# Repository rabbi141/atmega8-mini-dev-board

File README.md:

# AVR ATmega8 Mini Devlopment Board

The PCB of this board is designed with KiCad V5

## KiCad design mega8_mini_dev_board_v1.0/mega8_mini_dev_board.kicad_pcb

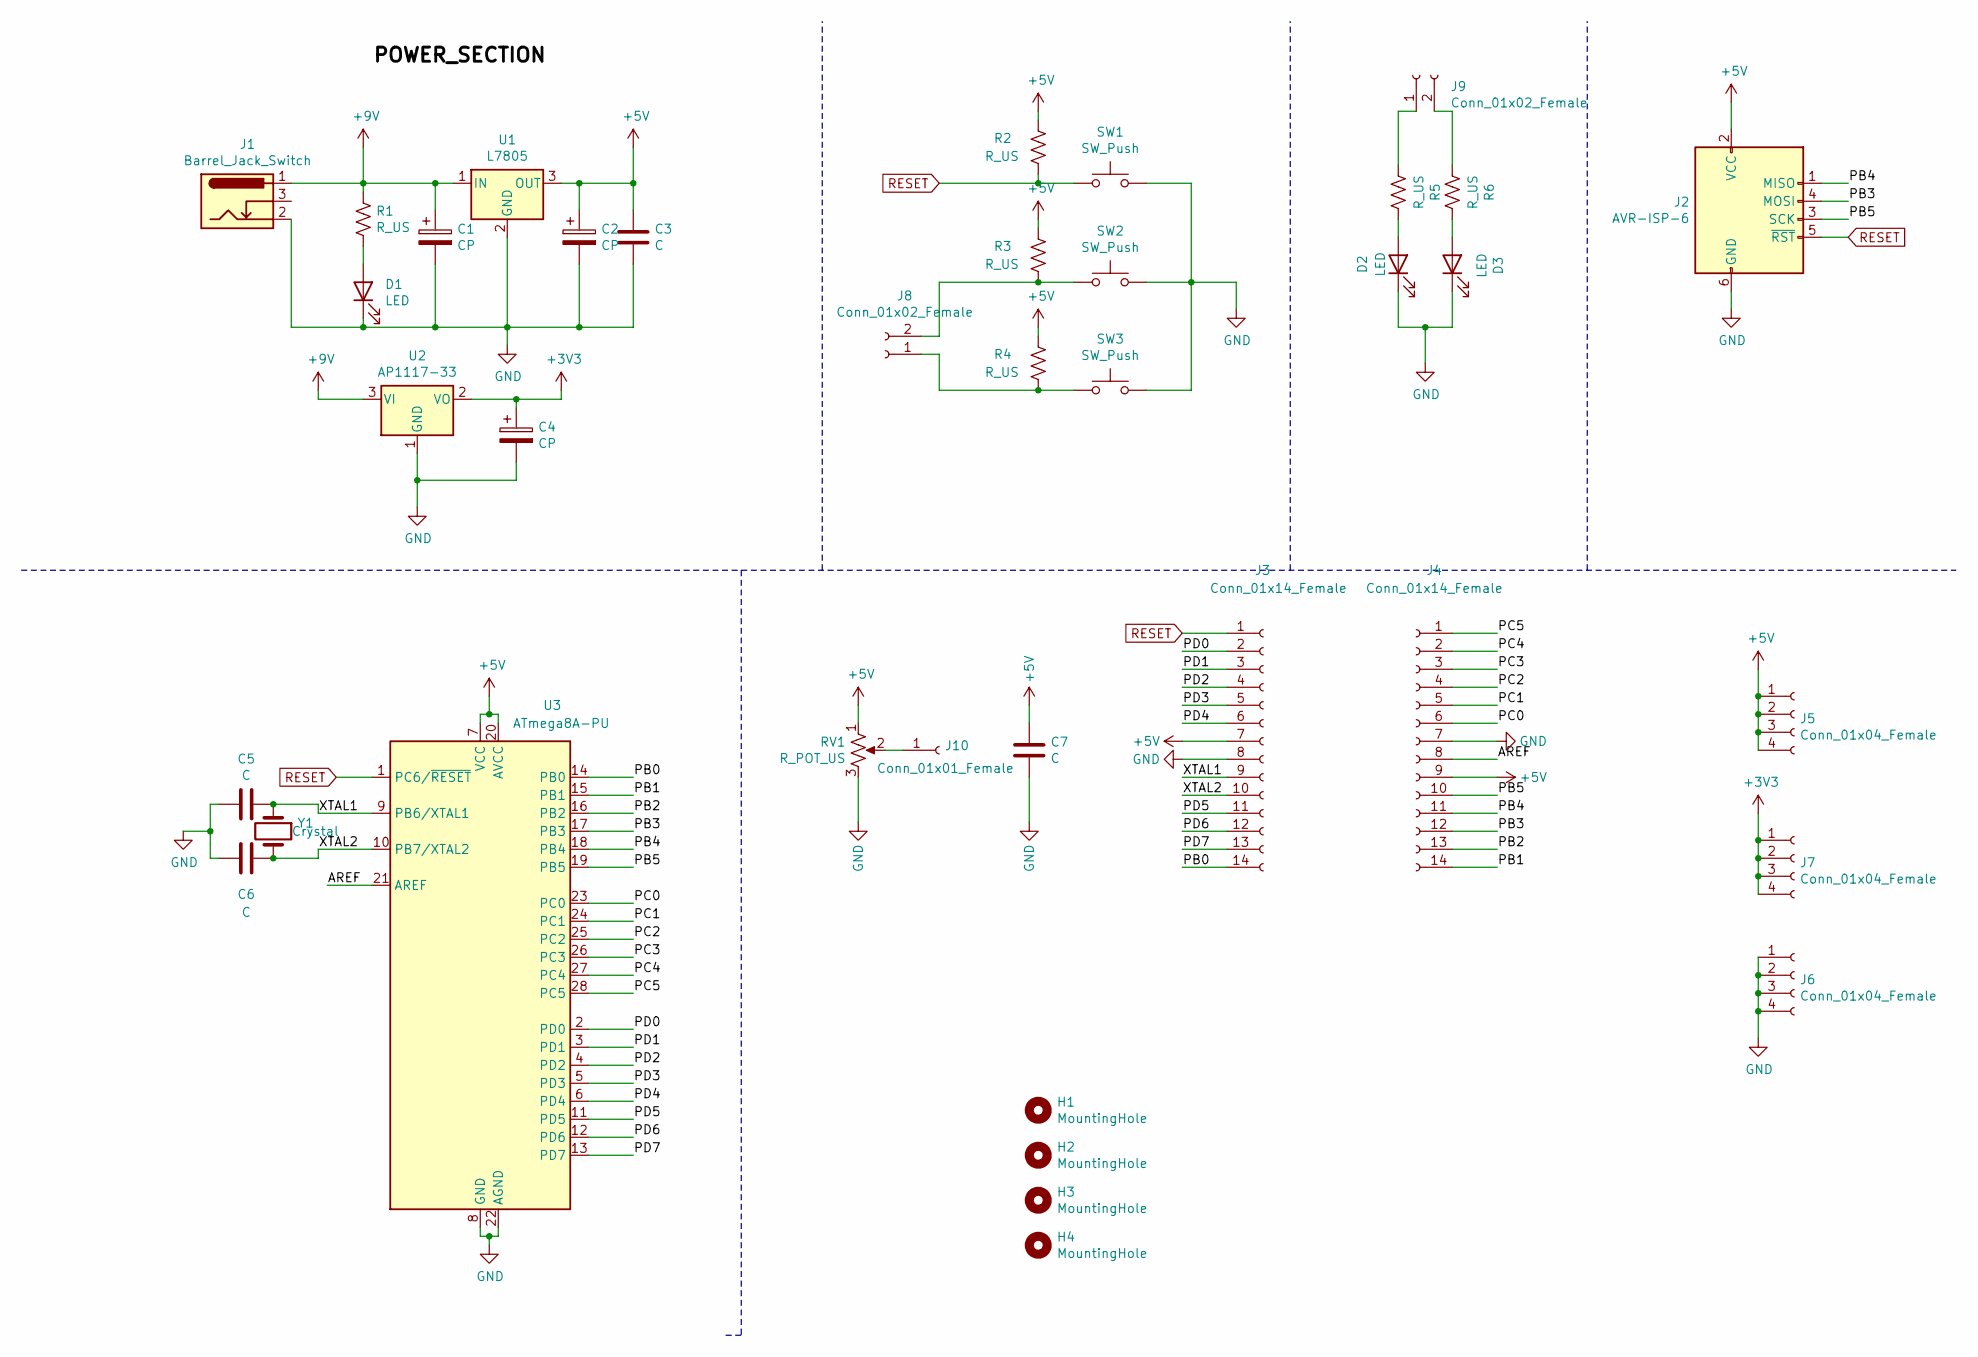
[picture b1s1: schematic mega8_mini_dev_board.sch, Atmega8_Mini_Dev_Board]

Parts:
C1, C2, C4: CP; CP_Radial_D6.3mm_P2.50mm
C3, C5, C6, C7: C; C_Disc_D5.0mm_W2.5mm_P2.50mm
D1, D2, D3: LED; LED_D3.0mm
H1, H2, H3, H4: MountingHole; MountingHole_3mm_Pad
J1: Barrel_Jack_Switch; BarrelJack_Horizontal
J2: AVR-ISP-6; IDC-Header_2x03_P2.54mm_Vertical
J3, J4: Conn_01x14_Female; PinSocket_1x14_P2.54mm_Vertical
J5, J6, J7: Conn_01x04_Female; PinSocket_1x04_P2.54mm_Vertical
J8, J9: Conn_01x02_Female; PinSocket_1x02_P2.54mm_Vertical
J10: Conn_01x01_Female; PinSocket_1x01_P2.54mm_Vertical
R1, R2, R3, R4, R5, R6: R_US; R_Axial_DIN0207_L6.3mm_D2.5mm_P10.16mm_Horizontal
RV1: R_POT_US; Potentiometer_ACP_CA9-V10_Vertical
SW1, SW2, SW3: SW_Push; SW_PUSH_6mm
U1: L7805; TO-220-3_Vertical
U2: AP1117-33; SOT-223-3_TabPin2
U3: ATmega8A-PU; DIP-28_W7.62mm
Y1: Crystal; Crystal_HC52-8mm_Vertical

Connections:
+3V3: C4.1, J7.1, J7.2, J7.3, J7.4, U2.2 (VO)
+5V: C2.1, C3.1, C7.1, J2.2 (VCC), J3.7, J4.9, J5.1, J5.2, J5.3, J5.4, R2.2, R3.2, R4.2, RV1.1, U1.3 (OUT), U3.7 (VCC), U3.20 (AVCC)
+9V: C1.1, J1.1, R1.2, U1.1 (IN), U2.3 (VI)
/AREF: J4.8, U3.21 (AREF)
/PB0: J3.14, U3.14 (PB0)
/PB1: J4.14, U3.15 (PB1)
/PB2: J4.13, U3.16 (PB2)
/PB3: J2.4 (MOSI), J4.12, U3.17 (PB3)
/PB4: J2.1 (MISO), J4.11, U3.18 (PB4)
/PB5: J2.3 (SCK), J4.10, U3.19 (PB5)
/PC0: J4.6, U3.23 (PC0)
/PC1: J4.5, U3.24 (PC1)
/PC2: J4.4, U3.25 (PC2)
/PC3: J4.3, U3.26 (PC3)
/PC4: J4.2, U3.27 (PC4)
/PC5: J4.1, U3.28 (PC5)
/PD0: J3.2, U3.2 (PD0)
/PD1: J3.3, U3.3 (PD1)
/PD2: J3.4, U3.4 (PD2)
/PD3: J3.5, U3.5 (PD3)
/PD4: J3.6, U3.6 (PD4)
/PD5: J3.11, U3.11 (PD5)
/PD6: J3.12, U3.12 (PD6)
/PD7: J3.13, U3.13 (PD7)
/XTAL1: C5.1, J3.9, U3.9 (PB6/XTAL1), Y1.1
/XTAL2: C6.1, J3.10, U3.10 (PB7/XTAL2), Y1.2
GND: C1.2, C2.2, C3.2, C4.2, C5.2, C6.2, C7.2, D1.1 (K), D2.1 (K), D3.1 (K), J1.2, J2.6 (GND), J3.8, J4.7, J6.1, J6.2, J6.3, J6.4, RV1.3, SW1.2, SW2.2, SW3.2, U1.2 (GND), U2.1 (GND), U3.8 (GND), U3.22 (AGND)
unnamed: D1.2 (A), R1.1
unnamed: D2.2 (A), R5.2
unnamed: D3.2 (A), R6.2
unnamed: J8.1, R4.1, SW3.1
unnamed: J8.2, R3.1, SW2.1
unnamed: J9.1, R5.1
unnamed: J9.2, R6.1
unnamed: J10.1, RV1.2
RESET: J2.5 (~RST), J3.1, R2.1, SW1.1, U3.1 (PC6/~RESET)

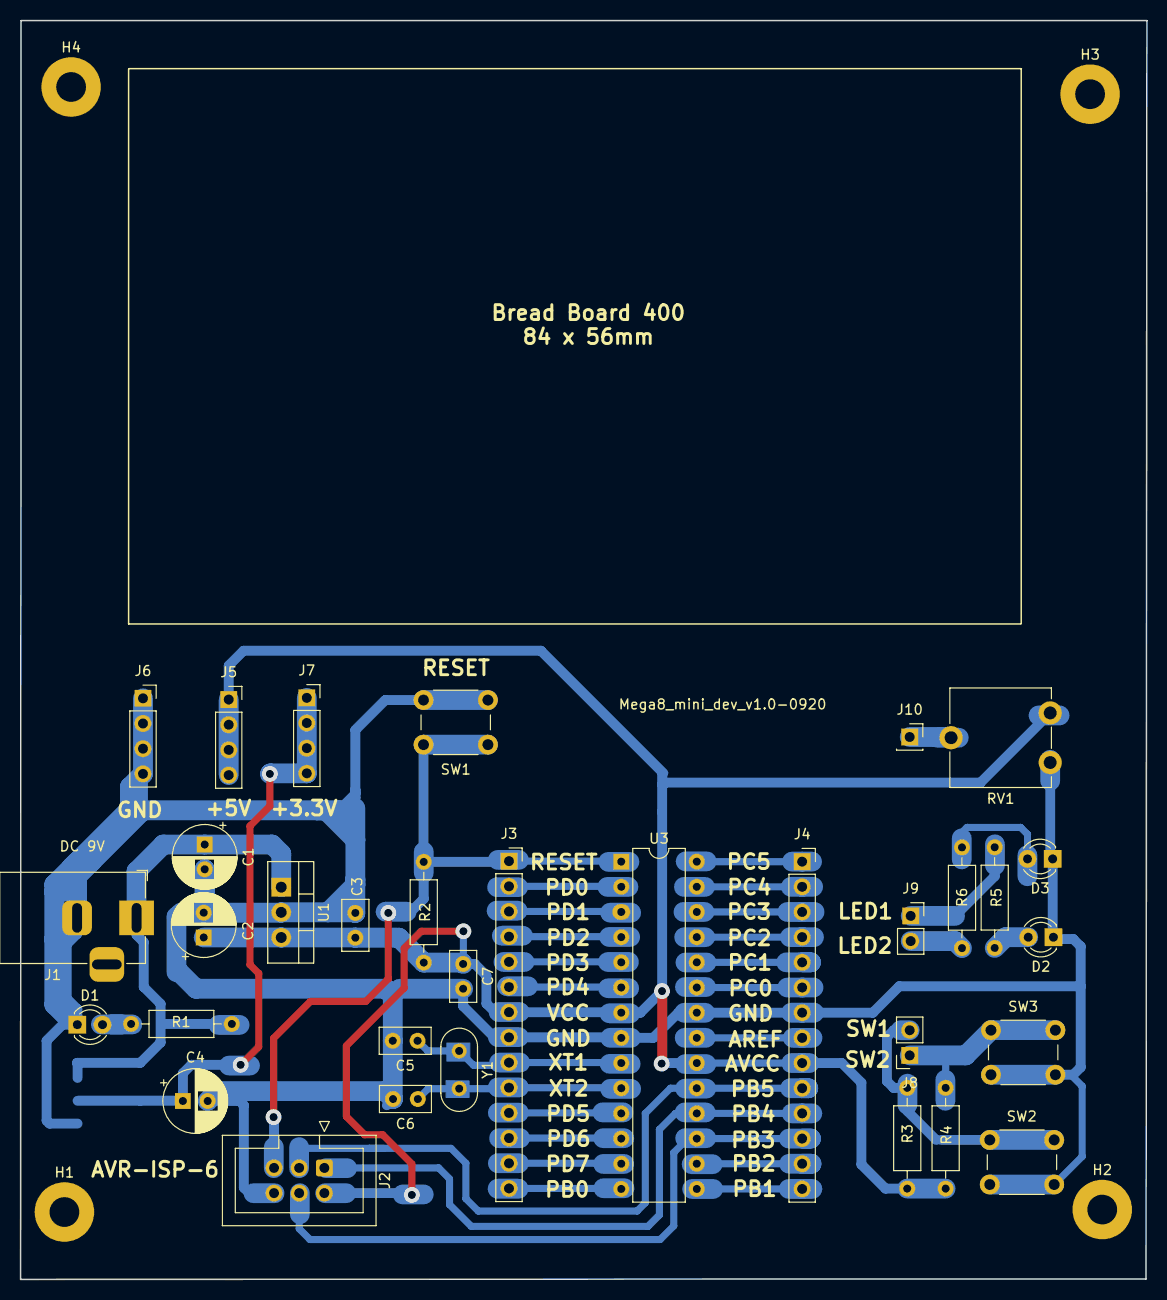
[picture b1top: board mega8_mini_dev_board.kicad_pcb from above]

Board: 2 copper layers, 113.6 x 127.0 mm, 38 parts (1 on the bottom side), 36 nets.

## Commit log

2020-09-26 Image Folder Added
2020-09-29 Some pad size chaged
2020-10-09 Some Track clearence corrected
2021-09-15 Added real board image
2021-09-15 Real board image added
